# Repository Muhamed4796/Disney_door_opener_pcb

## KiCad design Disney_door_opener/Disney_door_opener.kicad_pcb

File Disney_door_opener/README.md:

# Disney_door_opener_pcb
# Disney_door_opener_pcb

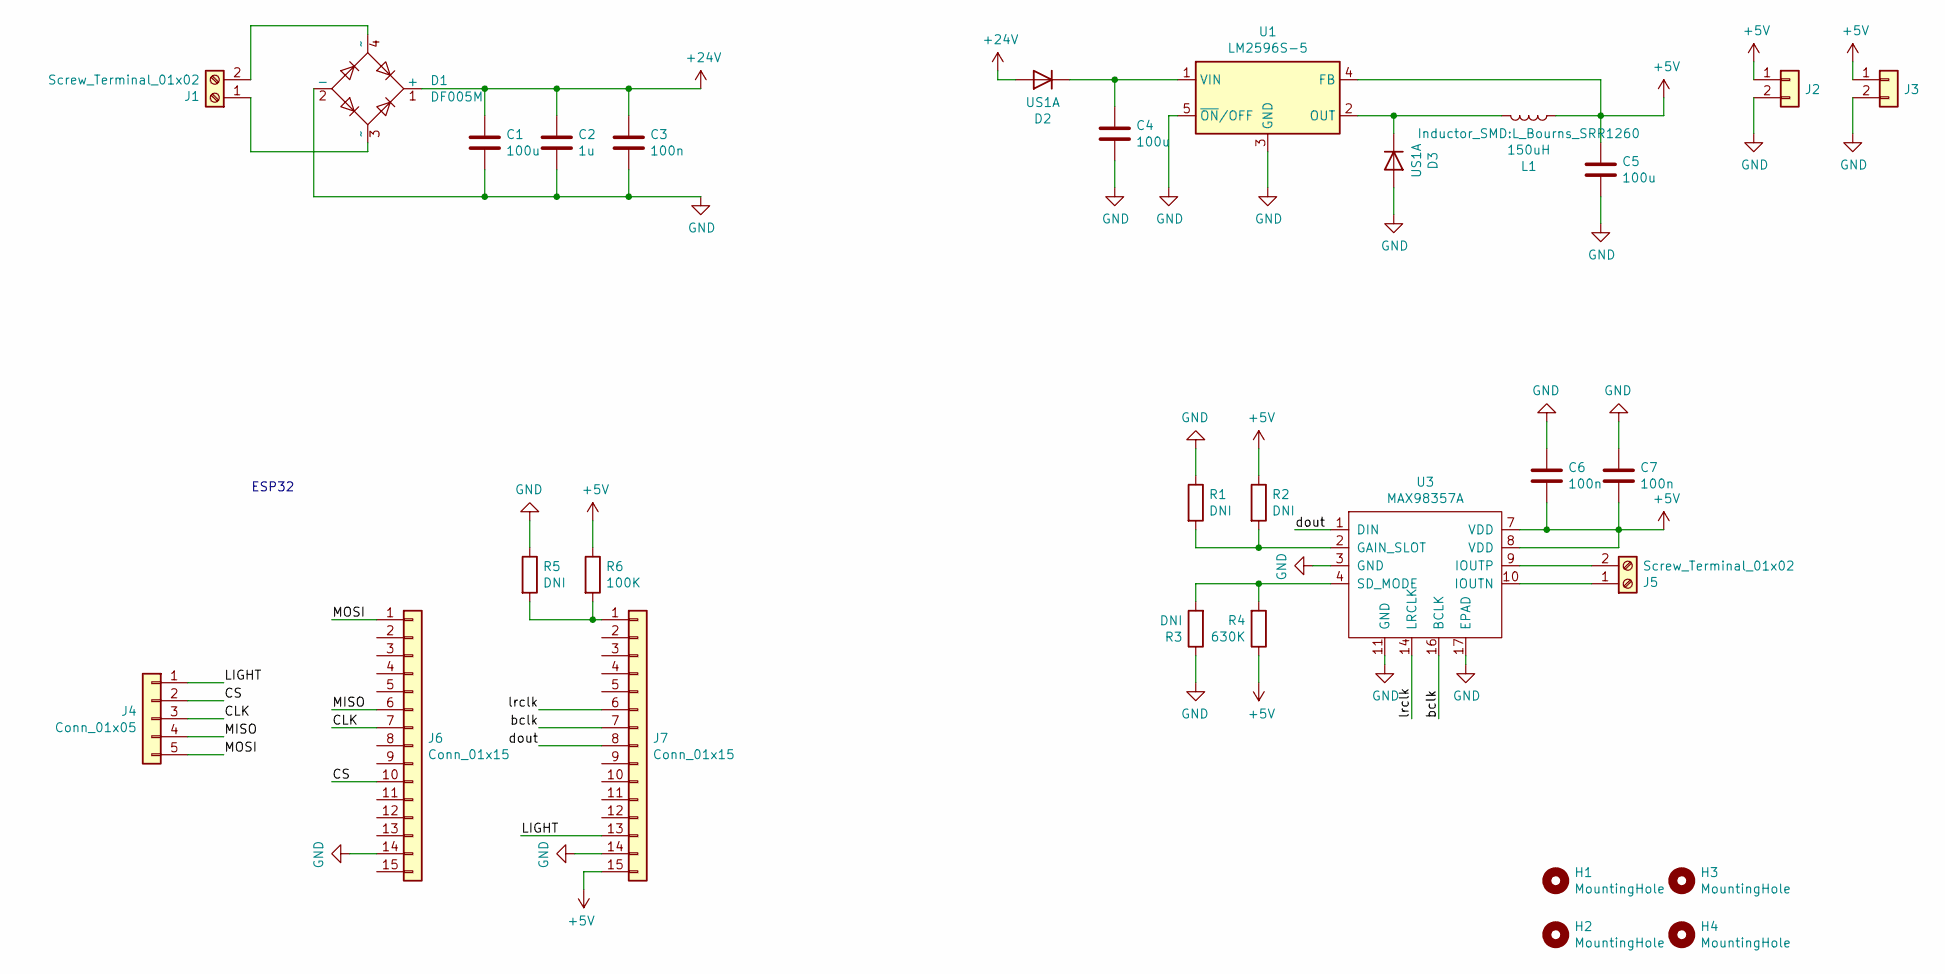
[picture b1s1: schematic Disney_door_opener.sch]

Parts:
C1, C4, C5: 100u; CP_Elec_5x5.3
C2: 1u; C_1206_3216Metric_Pad1.33x1.80mm_HandSolder
C3, C6, C7: 100n; C_1206_3216Metric_Pad1.33x1.80mm_HandSolder
D1: DF005M; Diode_Bridge_DIP-4_W7.62mm_P5.08mm
D2, D3: US1A; D_SMA
H1, H2, H3, H4: MountingHole; MountingHole_2.2mm_M2
J1, J5: Screw_Terminal_01x02; TerminalBlock_bornier-2_P5.08mm
J2, J3: Conn_01x02; PinSocket_1x02_P2.54mm_Vertical
J4: Conn_01x05; PinHeader_1x05_P2.54mm_Vertical
J6, J7: Conn_01x15; PinSocket_1x15_P2.54mm_Vertical
L1: 150uH; L_Bourns_SRR1260
R1, R2, R3, R5: DNI; R_1206_3216Metric_Pad1.30x1.75mm_HandSolder
R4: 630K; R_1206_3216Metric_Pad1.30x1.75mm_HandSolder
R6: 100K; R_1206_3216Metric_Pad1.30x1.75mm_HandSolder
U1: LM2596S-5; TO-263-5_TabPin3
U3: MAX98357A; TQFN-16-1EP_3x3mm_P0.5mm_EP1.23x1.23mm_ThermalVias

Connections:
+5V: C5.1, C6.2, C7.2, J2.1, J3.1, J7.15, L1.1, R2.1, R4.1, R6.1, U1.4 (FB), U3.7 (VDD), U3.8 (VDD)
+24V: C1.1, C2.1, C3.1, D1.1 (+), D2.2 (A)
/CLK: J4.3, J6.7
/CS: J4.2, J6.10
/LIGHT: J4.1, J7.13
/MISO: J4.4, J6.6
/MOSI: J4.5, J6.1
/bclk: J7.7, U3.16 (BCLK)
/dout: J7.8, U3.1 (DIN)
/lrclk: J7.6, U3.14 (LRCLK)
GND: C1.2, C2.2, C3.2, C4.2, C5.2, C6.1, C7.1, D1.2 (-), D3.2 (A), J2.2, J3.2, J6.14, J7.14, R1.1, R3.1, R5.1, U1.3 (GND), U1.5 (~ON~/OFF), U3.3 (GND), U3.11 (GND), U3.17 (EPAD)
unnamed: C4.1, D2.1 (K), U1.1 (VIN)
unnamed: D1.3 (~~), J1.1
unnamed: D1.4 (~~), J1.2
unnamed: D3.1 (K), L1.2, U1.2 (OUT)
unnamed: J5.1, U3.10 (IOUTN)
unnamed: J5.2, U3.9 (IOUTP)
unnamed: J7.1, R5.2, R6.2
unnamed: R1.2, R2.2, U3.2 (GAIN_SLOT)
unnamed: R3.2, R4.2, U3.4 (SD_MODE)

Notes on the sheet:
ESP32

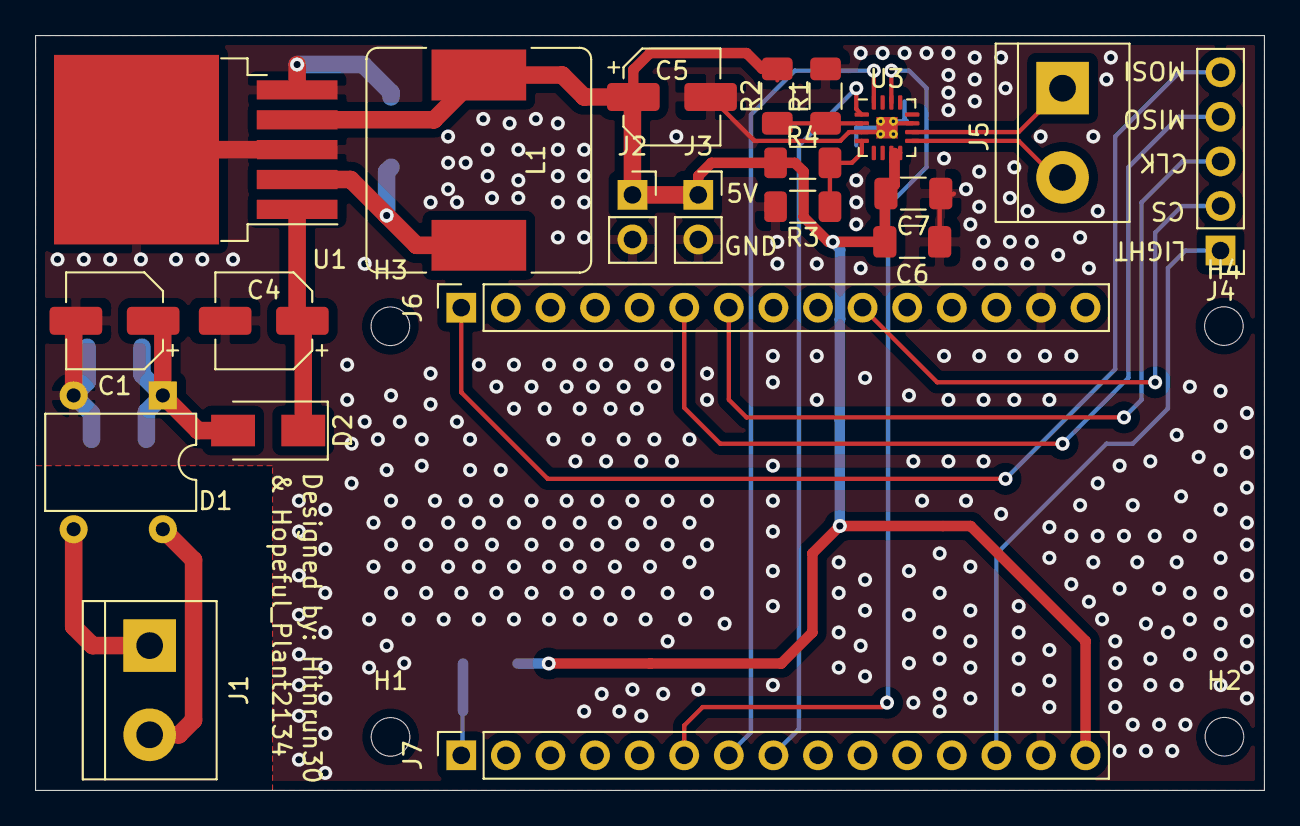
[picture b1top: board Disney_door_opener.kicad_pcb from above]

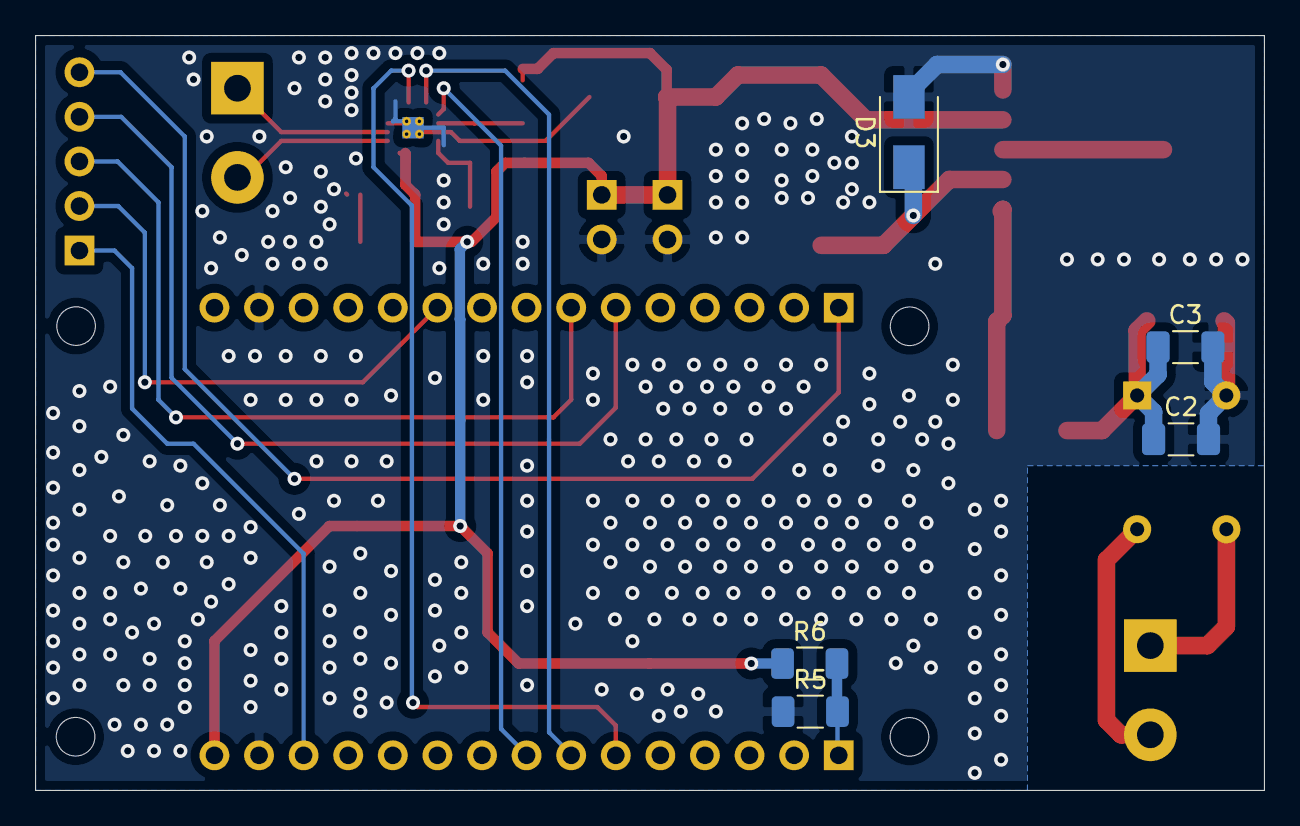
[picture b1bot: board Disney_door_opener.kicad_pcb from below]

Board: 2 copper layers, 70.0 x 43.0 mm, 30 parts (5 on the bottom side), 20 nets.

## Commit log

2023-05-28 Added initial KiCAD files
2023-06-11 Changed esp32 board with 2 pinheader connectors. Updated resistor values for proper operation.
2023-06-15 Corrected swapped pins.
2023-06-16 Minor corrections. Changed pin headers to female.
2023-07-02 Removed one via and checked schematic and layout once more.
